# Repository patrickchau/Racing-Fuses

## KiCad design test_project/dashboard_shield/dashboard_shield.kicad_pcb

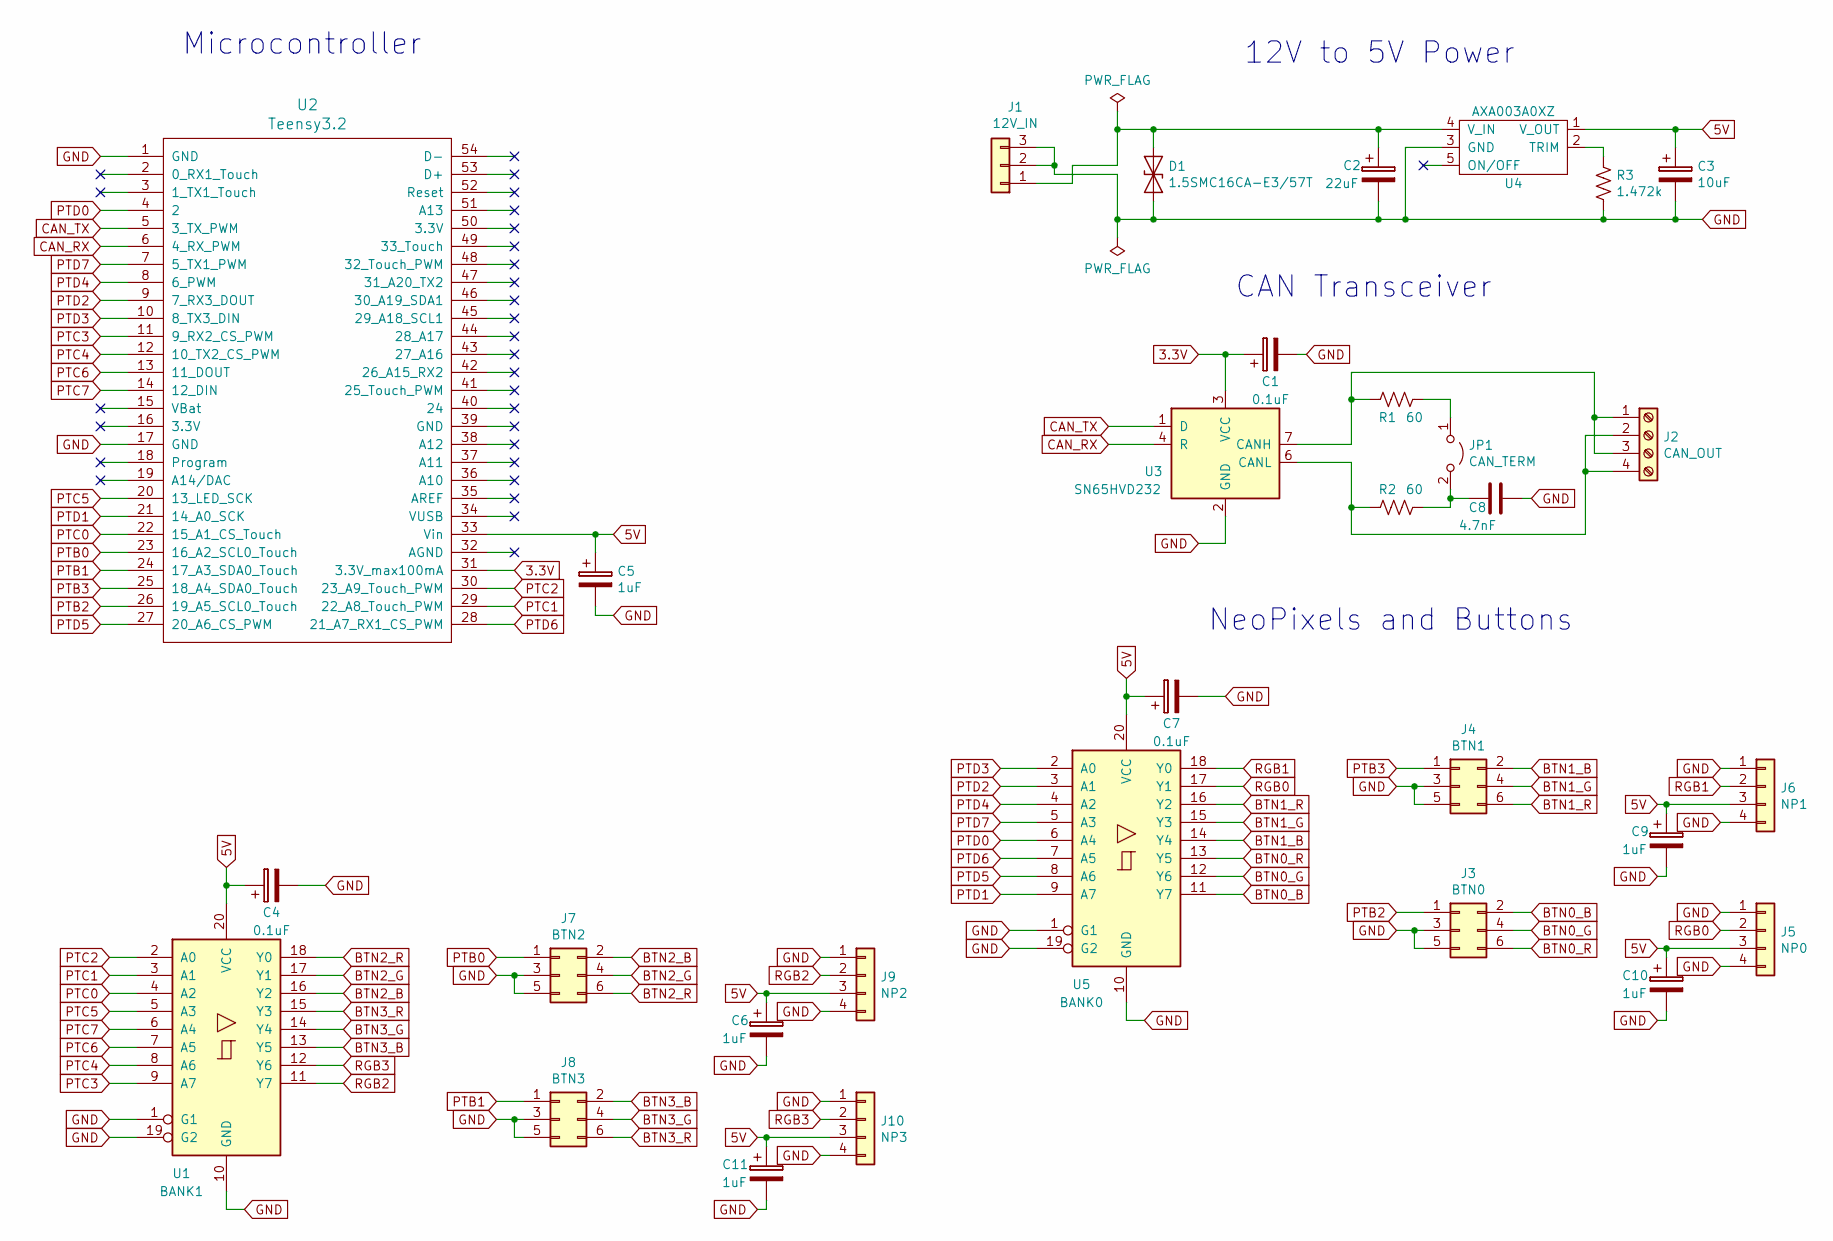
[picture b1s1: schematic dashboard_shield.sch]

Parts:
C1, C4, C7: 0.1uF; C_0402_1005Metric
C2: 22uF; C_0805_2012Metric
C3: 10uF; C_0402_1005Metric
C5, C6, C9, C10, C11: 1uF; C_0402_1005Metric
C8: 4.7nF; C_0402_1005Metric
D1: 1.5SMC16CA-E3/57T; DO-214AB
J1: 12V_IN; BarrelJack_CUI_PJ-102AH_Horizontal
J2: CAN_OUT; PinHeader_1x04_P2.54mm_Vertical
J3: BTN0; PinHeader_2x03_P2.54mm_Vertical
J4: BTN1; PinHeader_2x03_P2.54mm_Vertical
J5: NP0; PinHeader_1x04_P2.54mm_Vertical
J6: NP1; PinHeader_1x04_P2.54mm_Vertical
J7: BTN2; PinHeader_2x03_P2.54mm_Vertical
J8: BTN3; PinHeader_2x03_P2.54mm_Vertical
J9: NP2; PinHeader_1x04_P2.54mm_Vertical
J10: NP3; PinHeader_1x04_P2.54mm_Vertical
JP1: CAN_TERM; PinHeader_1x02_P2.54mm_Vertical
R1, R2: 60; R_0402_1005Metric
R3: 1.472k; R_0402_1005Metric
U1: BANK1; SOIC-20W_7.5x12.8mm_P1.27mm
U2: Teensy3.2; Teensy30_31_32_LC
U3: SN65HVD232; SOIC-8_3.9x4.9mm_P1.27mm
U4: AXA003A0XZ
U5: BANK0; SOIC-20W_7.5x12.8mm_P1.27mm

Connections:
3.3V: C1.1, U2.31 (3.3V_max100mA), U3.3 (VCC)
5V: C3.1, C4.1, C5.1, C6.1, C7.1, C9.1, C10.1, C11.1, J5.3, J6.3, J9.3, J10.3, U1.20 (VCC), U2.33 (Vin), U4.1 (V_OUT), U5.20 (VCC)
BTN0_B: J3.2, U5.11 (Y7)
BTN0_G: J3.4, U5.12 (Y6)
BTN0_R: J3.6, U5.13 (Y5)
BTN1_B: J4.2, U5.14 (Y4)
BTN1_G: J4.4, U5.15 (Y3)
BTN1_R: J4.6, U5.16 (Y2)
BTN2_B: J7.2, U1.16 (Y2)
BTN2_G: J7.4, U1.17 (Y1)
BTN2_R: J7.6, U1.18 (Y0)
BTN3_B: J8.2, U1.13 (Y5)
BTN3_G: J8.4, U1.14 (Y4)
BTN3_R: J8.6, U1.15 (Y3)
CAN_RX: U2.6 (4_RX_PWM), U3.4 (R)
CAN_TX: U2.5 (3_TX_PWM), U3.1 (D)
GND: C1.2, C2.2, C3.2, C4.2, C5.2, C6.2, C7.2, C8.1, C9.2, C10.2, C11.2, D1.1 (A1), J1.2, J1.3, J3.3, J3.5, J4.3, J4.5, J5.1, J5.4, J6.1, J6.4, J7.3, J7.5, J8.3, J8.5, J9.1, J9.4, J10.1, J10.4, R3.2, U1.1 (G1), U1.10 (GND), U1.19 (G2), U2.1 (GND), U2.17 (GND), U3.2 (GND), U4.3 (GND), U5.1 (G1), U5.10 (GND), U5.19 (G2)
unnamed: C2.1, D1.2 (A2), J1.1, U4.4 (V_IN)
unnamed: C8.2, JP1.2 (B), R2.1
unnamed: J2.1, J2.3, R1.2, U3.7 (CANH)
unnamed: J2.2, J2.4, R2.2, U3.6 (CANL)
unnamed: JP1.1 (A), R1.1
unnamed: R3.1, U4.2 (TRIM)
PTB0: J7.1, U2.23 (16_A2_SCL0_Touch)
PTB1: J8.1, U2.24 (17_A3_SDA0_Touch)
PTB2: J3.1, U2.26 (19_A5_SCL0_Touch)
PTB3: J4.1, U2.25 (18_A4_SDA0_Touch)
PTC0: U1.4 (A2), U2.22 (15_A1_CS_Touch)
PTC1: U1.3 (A1), U2.29 (22_A8_Touch_PWM)
PTC2: U1.2 (A0), U2.30 (23_A9_Touch_PWM)
PTC3: U1.9 (A7), U2.11 (9_RX2_CS_PWM)
PTC4: U1.8 (A6), U2.12 (10_TX2_CS_PWM)
PTC5: U1.5 (A3), U2.20 (13_LED_SCK)
PTC6: U1.7 (A5), U2.13 (11_DOUT)
PTC7: U1.6 (A4), U2.14 (12_DIN)
PTD0: U2.4 (2), U5.6 (A4)
PTD1: U2.21 (14_A0_SCK), U5.9 (A7)
PTD2: U2.9 (7_RX3_DOUT), U5.3 (A1)
PTD3: U2.10 (8_TX3_DIN), U5.2 (A0)
PTD4: U2.8 (6_PWM), U5.4 (A2)
PTD5: U2.27 (20_A6_CS_PWM), U5.8 (A6)
PTD6: U2.28 (21_A7_RX1_CS_PWM), U5.7 (A5)
PTD7: U2.7 (5_TX1_PWM), U5.5 (A3)
RGB0: J5.2, U5.17 (Y1)
RGB1: J6.2, U5.18 (Y0)
RGB2: J9.2, U1.11 (Y7)
RGB3: J10.2, U1.12 (Y6)

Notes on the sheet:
12V to 5V Power
CAN Transceiver
NeoPixels and Buttons
Microcontroller

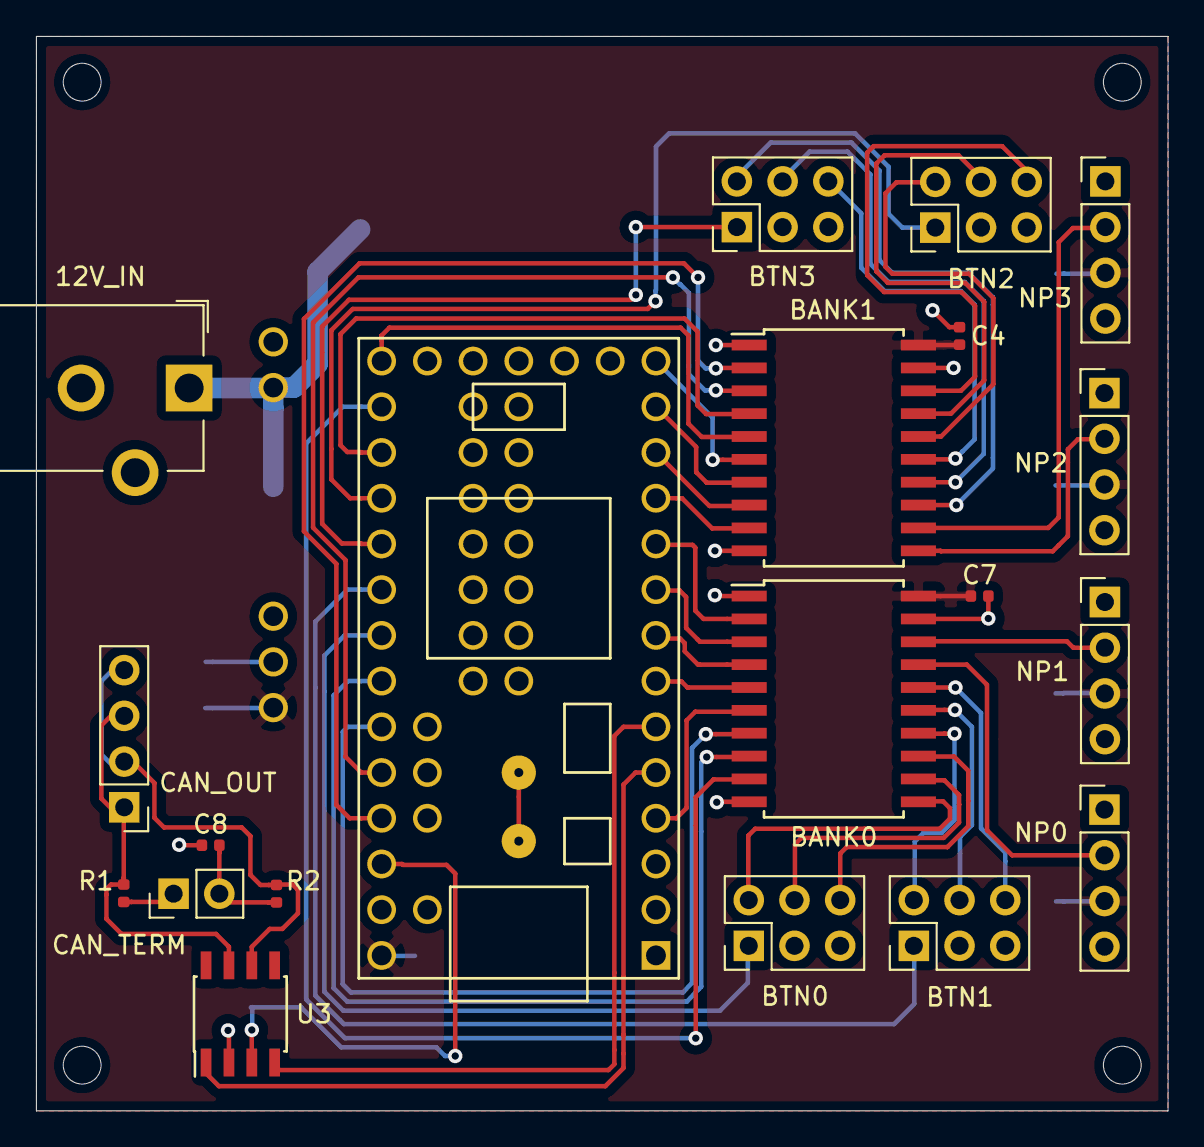
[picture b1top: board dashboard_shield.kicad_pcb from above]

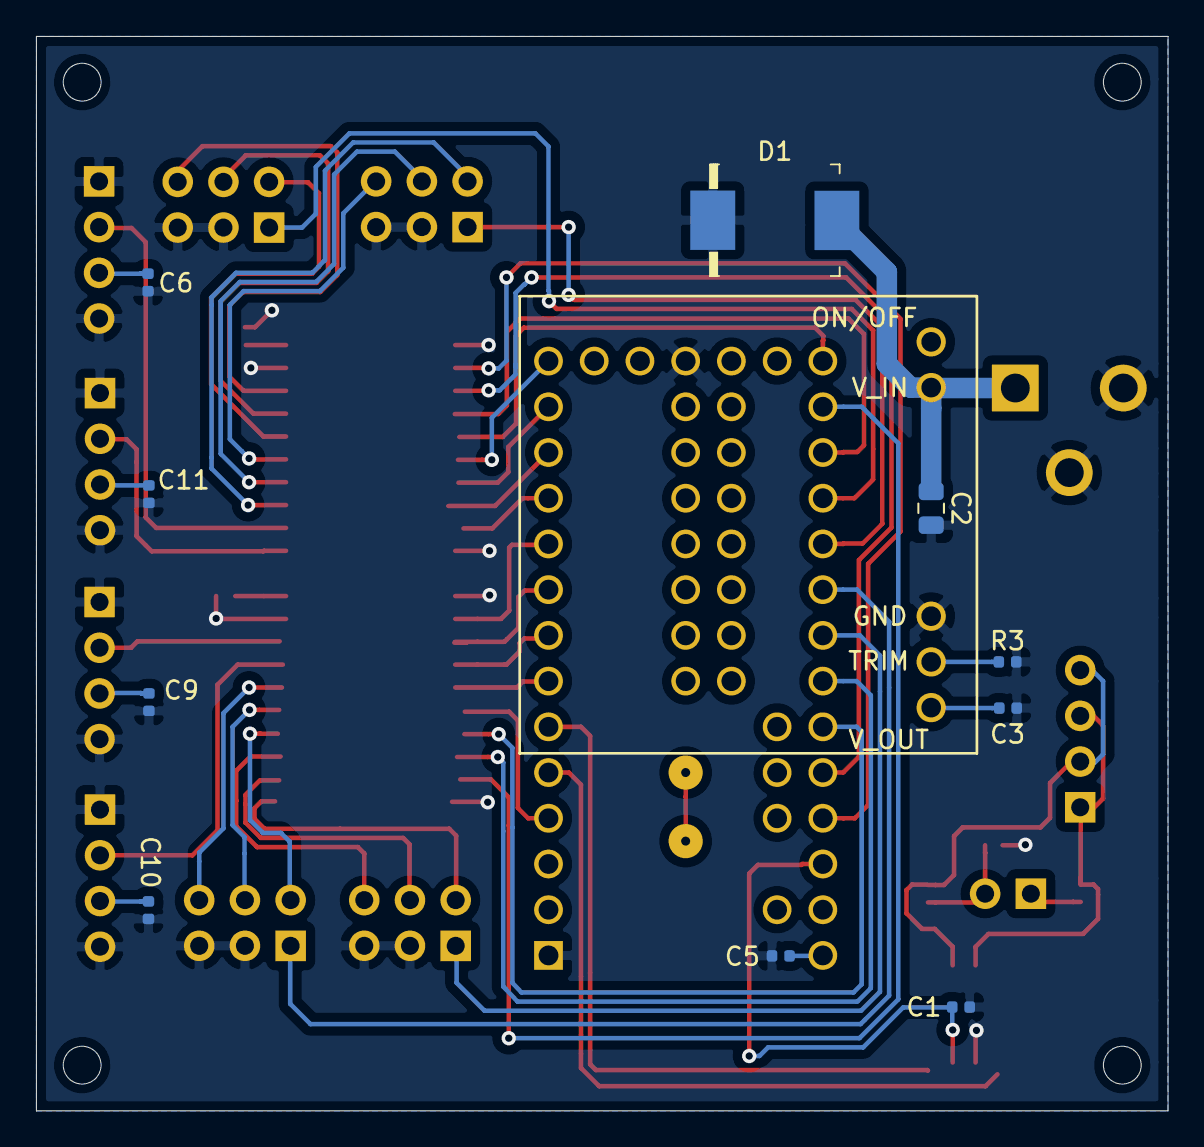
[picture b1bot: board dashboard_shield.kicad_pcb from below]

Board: 2 copper layers, 62.9 x 59.7 mm, 31 parts (11 on the bottom side), 47 nets.

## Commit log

2020-01-30 excel
2020-01-31 work in progress
2020-03-20 replaced relays with n-channel fets
2020-03-20 added ltspice
